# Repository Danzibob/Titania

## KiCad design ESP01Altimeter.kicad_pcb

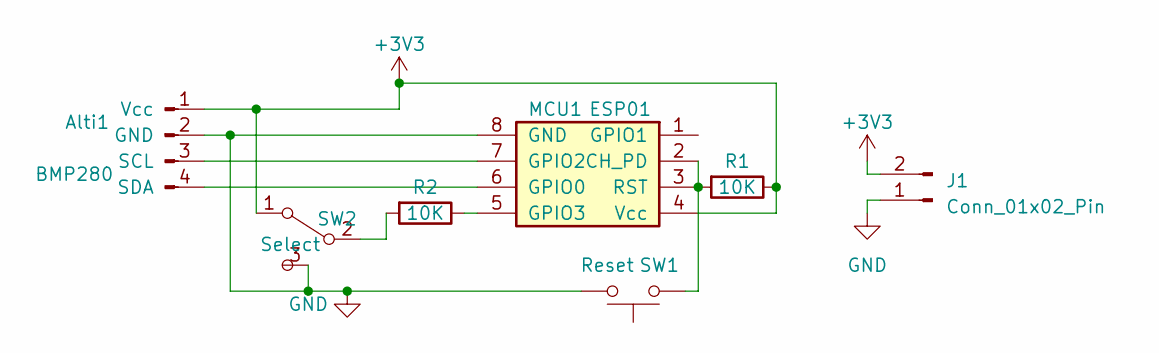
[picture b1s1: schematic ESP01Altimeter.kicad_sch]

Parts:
Alti1: BMP280; PinHeader_1x04_P2.54mm_Vertical
J1: Conn_01x02_Pin; JST_PH_S2B-PH-K_1x02_P2.00mm_Horizontal
MCU1: ESP01; PinHeader_2x04_P2.54mm_Vertical
R1, R2: 10K; R_Axial_DIN0204_L3.6mm_D1.6mm_P7.62mm_Horizontal
SW1: Reset; SW_PUSH_6mm
SW2: Select; 3_pin_toggle_switch

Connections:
+3V3: Alti1.1 (Vcc), J1.2, MCU1.4 (Vcc), R1.1, SW2.1 (A)
GND: Alti1.2 (GND), J1.1, MCU1.8 (GND), SW1.2, SW2.3 (C)
unnamed: Alti1.3 (SCL), MCU1.7 (GPIO2)
unnamed: Alti1.4 (SDA), MCU1.6 (GPIO0)
unnamed: MCU1.2 (CH_PD), MCU1.3 (RST), R1.2, SW1.1
unnamed: MCU1.5 (GPIO3), R2.1
unnamed: R2.2, SW2.2 (B)

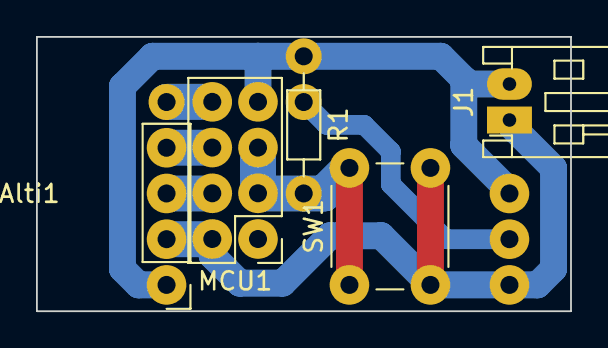
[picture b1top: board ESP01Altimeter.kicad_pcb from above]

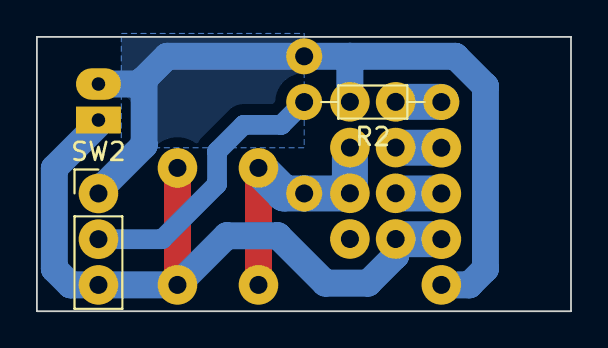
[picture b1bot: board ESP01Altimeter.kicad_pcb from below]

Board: 2 copper layers, 29.7 x 15.2 mm, 7 parts (2 on the bottom side), 7 nets.

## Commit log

2023-06-19 First working version
2023-06-20 V0.2
